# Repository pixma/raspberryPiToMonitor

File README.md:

raspberryPiToMonitor
====================

An Energy monitoring System based on RaspberryPi B Model.

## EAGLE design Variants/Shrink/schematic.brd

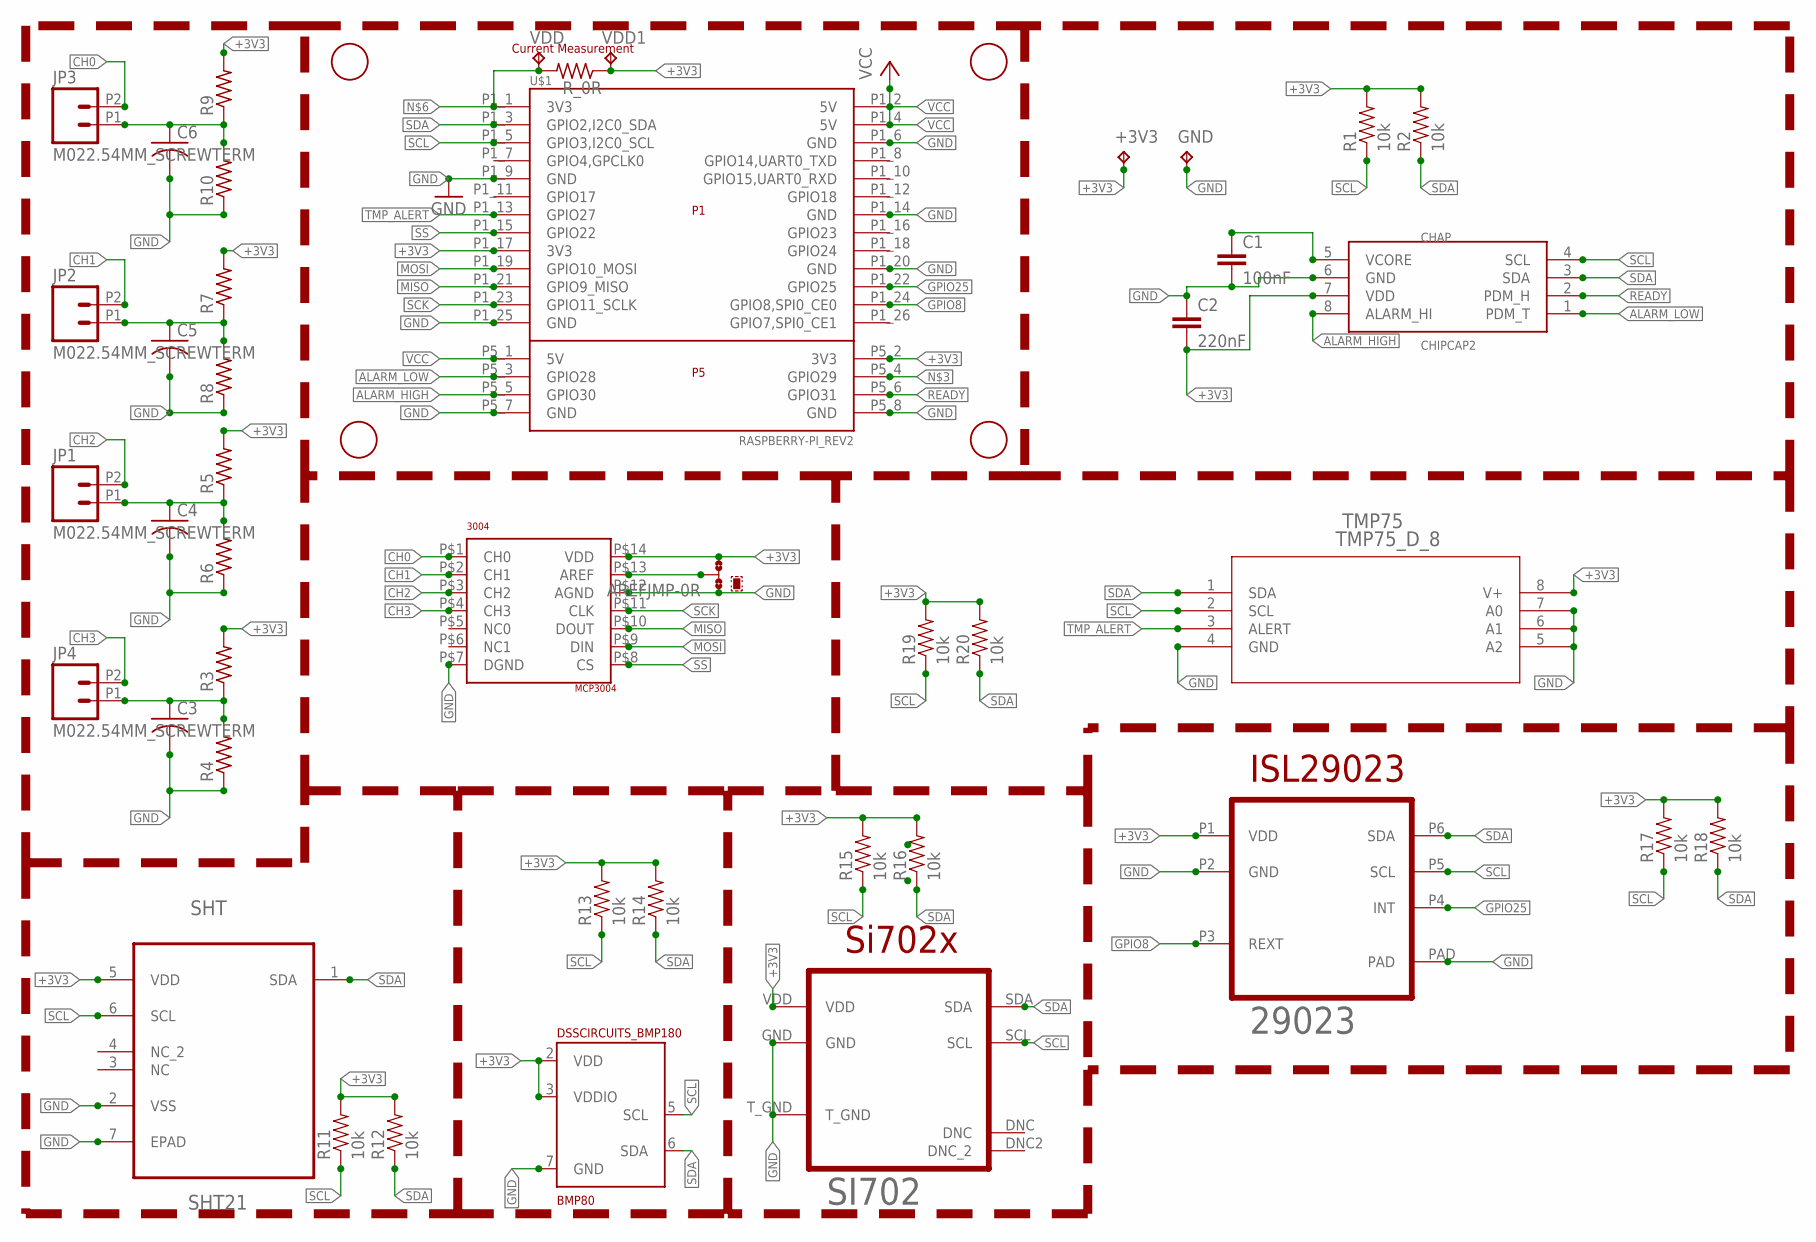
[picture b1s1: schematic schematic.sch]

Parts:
3004: MCP3004; TSSOP14_4MM4
29023: ISL29023; ODFN6
+3V3: TPTP20R; TP20R
AREFJMP: 0R-JUMPA; A0R-JMP
BMP80: DSSCIRCUITS_BMP180; DSSCIRCUITS_LGA7
C1: 100nF; 0402-CAP
C2: 220nF; 0402-CAP
C3, C4, C5, C6: C-USC0402; C0402
CHAP: CHIPCAP2
GND: TPTP20R; TP20R
JP1, JP2, JP3, JP4: M022.54MM_SCREWTERM; 1X02_2.54_SCREWTERM
R1, R2, R11, R12, R13, R14, R15, R16, R17, R18, R19, R20: 10k; 0603-RES
R3, R4, R5, R6, R7, R8, R9, R10: R-US_R0402; R0402
R_0R: R-US_R0402; R0402
SHT: SHT21; DFN300X300X110-7N
SI702: SI702X; DFN6
TMP75: TMP75_D_8; D8
U$1: RASPBERRY-PI_REV2
U$2, U$3, U$4, U$5: FIDUCIAL; FIDUCIAL_1MM
VDD, VDD1: TPTP20R; TP20R

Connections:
+3V3: 3004.P$14 (VDD), 29023.P1 (VDD), +3V3.TP, AREFJMP.3, BMP80.2 (VDD), BMP80.3 (VDDIO), C2.2, CHAP.7 (VDD), R1.2, R2.2, R3.2, R5.2, R7.2, R9.2, R11.2, R12.2, R13.2, R14.2, R15.2, R16.2, R17.2, R18.2, R19.2, R20.2, R_0R.1, SHT.5 (VDD), SI702.VDD, TMP75.8 (V+), U$1.P1_17 (3V3), U$1.P5_2 (3V3), VDD1.TP
ALARM_HIGH: CHAP.8 (ALARM_HI), U$1.P5_5 (GPIO30)
ALARM_LOW: CHAP.1 (PDM_T), U$1.P5_3 (GPIO28)
CH0: 3004.P$1 (CH0), JP3.P2 (2)
CH1: 3004.P$2 (CH1), JP2.P2 (2)
CH2: 3004.P$3 (CH2), JP1.P2 (2)
CH3: 3004.P$4 (CH3), JP4.P2 (2)
GND: 3004.P$7 (DGND), 3004.P$12 (AGND), 29023.P2 (GND), 29023.PAD, AREFJMP.1, BMP80.7 (GND), C1.2, C2.1, C3.2, C4.2, C5.2, C6.2, CHAP.6 (GND), GND.TP, R4.1, R6.1, R8.1, R10.1, SHT.2 (VSS), SHT.7 (EPAD), SI702.GND, SI702.T_GND, TMP75.4 (GND), TMP75.5 (A2), TMP75.6 (A1), TMP75.7 (A0), U$1.P1_6 (GND), U$1.P1_9 (GND), U$1.P1_14 (GND), U$1.P1_20 (GND), U$1.P1_25 (GND), U$1.P5_7 (GND), U$1.P5_8 (GND)
GPIO8: 29023.P3 (REXT), U$1.P1_24 (GPIO8,SPI0_CE0)
GPIO25: 29023.P4 (INT), U$1.P1_22 (GPIO25)
MISO: 3004.P$10 (DOUT), U$1.P1_21 (GPIO9_MISO)
MOSI: 3004.P$9 (DIN), U$1.P1_19 (GPIO10_MOSI)
unnamed: C4.1, JP1.P1 (1), R5.1, R6.2
unnamed: C5.1, JP2.P1 (1), R7.1, R8.2
unnamed: C6.1, JP3.P1 (1), R9.1, R10.2
unnamed: C1.1, CHAP.5 (VCORE)
unnamed: R_0R.2, U$1.P1_1 (3V3), VDD.TP
unnamed: C3.1, JP4.P1 (1), R3.1, R4.2
unnamed: 3004.P$13 (AREF), AREFJMP.2
READY: CHAP.2 (PDM_H), U$1.P5_6 (GPIO31)
SCK: 3004.P$11 (CLK), U$1.P1_23 (GPIO11_SCLK)
SCL: 29023.P5 (SCL), BMP80.5 (SCL), CHAP.4 (SCL), R1.1, R11.1, R13.1, R15.1, R17.1, R19.1, SHT.6 (SCL), SI702.SCL, TMP75.2 (SCL), U$1.P1_5 (GPIO3,I2C0_SCL)
SDA: 29023.P6 (SDA), BMP80.6 (SDA), CHAP.3 (SDA), R2.1, R12.1, R14.1, R16.1, R18.1, R20.1, SHT.1 (SDA), SI702.SDA, TMP75.1 (SDA), U$1.P1_3 (GPIO2,I2C0_SDA)
SS: 3004.P$8 (CS), U$1.P1_15 (GPIO22)
TMP_ALERT: TMP75.3 (ALERT), U$1.P1_13 (GPIO27)
VCC: U$1.P1_2 (5V), U$1.P1_4 (5V), U$1.P5_1 (5V)

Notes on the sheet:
Current Measurement

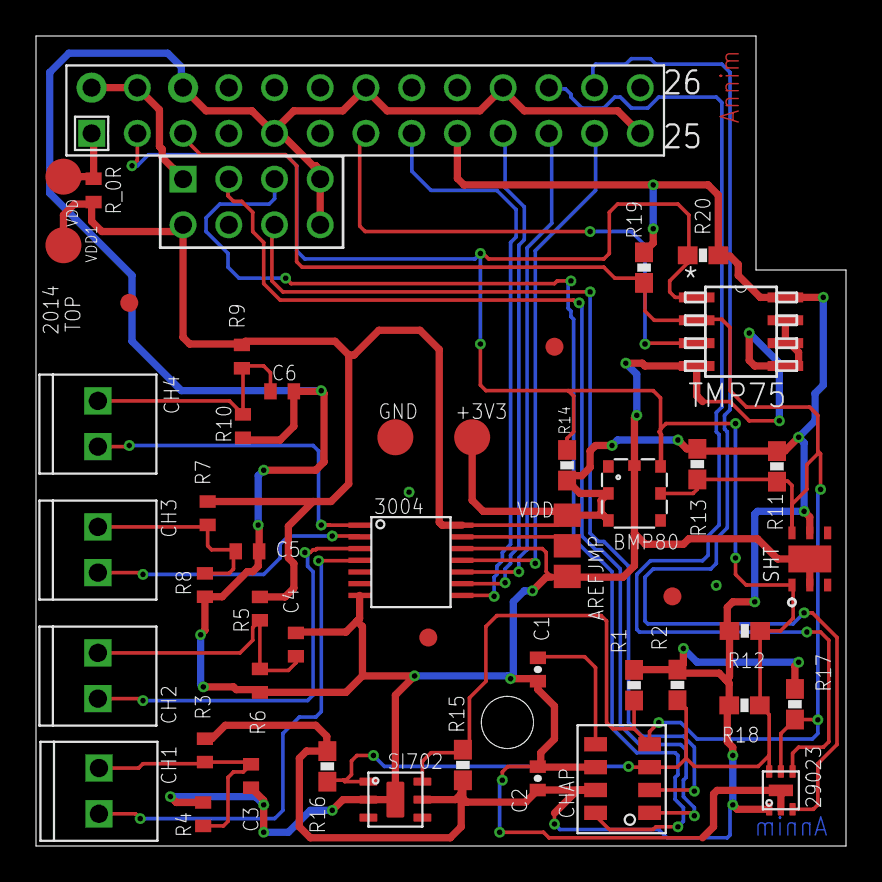
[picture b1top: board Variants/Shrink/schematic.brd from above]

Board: 2 copper layers, 45.0 x 45.0 mm, 48 parts (0 on the bottom side), 26 nets.

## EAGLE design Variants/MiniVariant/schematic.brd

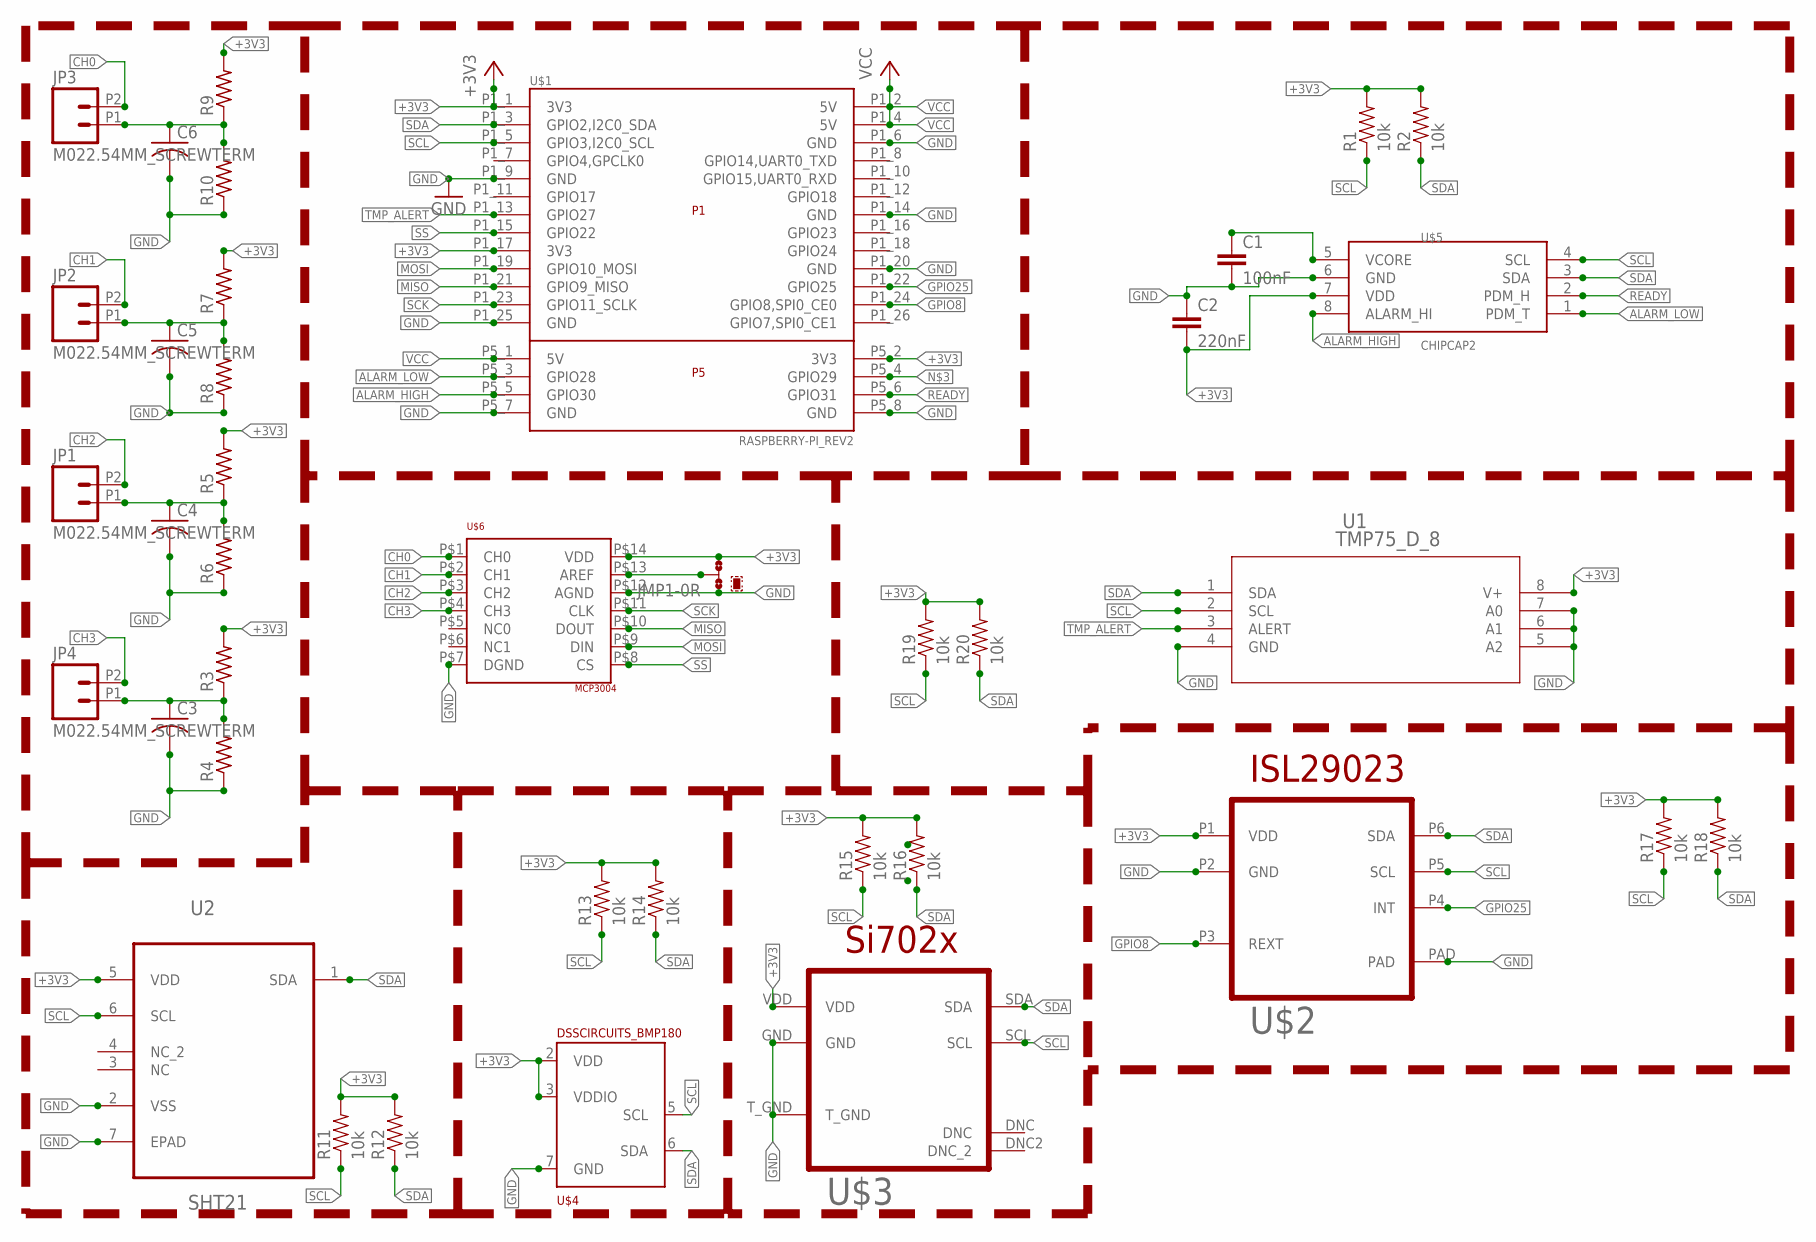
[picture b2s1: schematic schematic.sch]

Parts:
C1: 100nF; 0402-CAP
C2: 220nF; 0402-CAP
C3, C4, C5, C6: C-USC0402; C0402
JMP1: 0R-JUMPA; A0R-JMP
JP1, JP2, JP3, JP4: M022.54MM_SCREWTERM; 1X02_2.54_SCREWTERM
R1, R2, R11, R12, R13, R14, R15, R16, R17, R18, R19, R20: 10k; 0603-RES
R3, R4, R5, R6, R7, R8, R9, R10: R-US_R0402; R0402
U1: TMP75_D_8; D8
U2: SHT21; DFN300X300X110-7N
U$1: RASPBERRY-PI_REV2
U$2: ISL29023; ODFN6
U$3: SI702X; DFN6
U$4: DSSCIRCUITS_BMP180; DSSCIRCUITS_LGA7
U$5: CHIPCAP2
U$6: MCP3004; TSSOP14_4MM4

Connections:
+3V3: C2.2, JMP1.3, R1.2, R2.2, R3.2, R5.2, R7.2, R9.2, R11.2, R12.2, R13.2, R14.2, R15.2, R16.2, R17.2, R18.2, R19.2, R20.2, U1.8 (V+), U2.5 (VDD), U$1.P1_1 (3V3), U$1.P1_17 (3V3), U$1.P5_2 (3V3), U$2.P1 (VDD), U$3.VDD, U$4.2 (VDD), U$4.3 (VDDIO), U$5.7 (VDD), U$6.P$14 (VDD)
ALARM_HIGH: U$1.P5_5 (GPIO30), U$5.8 (ALARM_HI)
ALARM_LOW: U$1.P5_3 (GPIO28), U$5.1 (PDM_T)
CH0: JP3.P2 (2), U$6.P$1 (CH0)
CH1: JP2.P2 (2), U$6.P$2 (CH1)
CH2: JP1.P2 (2), U$6.P$3 (CH2)
CH3: JP4.P2 (2), U$6.P$4 (CH3)
GND: C1.2, C2.1, C3.2, C4.2, C5.2, C6.2, JMP1.1, R4.1, R6.1, R8.1, R10.1, U1.4 (GND), U1.5 (A2), U1.6 (A1), U1.7 (A0), U2.2 (VSS), U2.7 (EPAD), U$1.P1_6 (GND), U$1.P1_9 (GND), U$1.P1_14 (GND), U$1.P1_20 (GND), U$1.P1_25 (GND), U$1.P5_7 (GND), U$1.P5_8 (GND), U$2.P2 (GND), U$2.PAD, U$3.GND, U$3.T_GND, U$4.7 (GND), U$5.6 (GND), U$6.P$7 (DGND), U$6.P$12 (AGND)
GPIO8: U$1.P1_24 (GPIO8,SPI0_CE0), U$2.P3 (REXT)
GPIO25: U$1.P1_22 (GPIO25), U$2.P4 (INT)
MISO: U$1.P1_21 (GPIO9_MISO), U$6.P$10 (DOUT)
MOSI: U$1.P1_19 (GPIO10_MOSI), U$6.P$9 (DIN)
unnamed: C4.1, JP1.P1 (1), R5.1, R6.2
unnamed: C5.1, JP2.P1 (1), R7.1, R8.2
unnamed: C6.1, JP3.P1 (1), R9.1, R10.2
unnamed: C1.1, U$5.5 (VCORE)
unnamed: C3.1, JP4.P1 (1), R3.1, R4.2
unnamed: JMP1.2, U$6.P$13 (AREF)
READY: U$1.P5_6 (GPIO31), U$5.2 (PDM_H)
SCK: U$1.P1_23 (GPIO11_SCLK), U$6.P$11 (CLK)
SCL: R1.1, R11.1, R13.1, R15.1, R17.1, R19.1, U1.2 (SCL), U2.6 (SCL), U$1.P1_5 (GPIO3,I2C0_SCL), U$2.P5 (SCL), U$3.SCL, U$4.5 (SCL), U$5.4 (SCL)
SDA: R2.1, R12.1, R14.1, R16.1, R18.1, R20.1, U1.1 (SDA), U2.1 (SDA), U$1.P1_3 (GPIO2,I2C0_SDA), U$2.P6 (SDA), U$3.SDA, U$4.6 (SDA), U$5.3 (SDA)
SS: U$1.P1_15 (GPIO22), U$6.P$8 (CS)
TMP_ALERT: U1.3 (ALERT), U$1.P1_13 (GPIO27)
VCC: U$1.P1_2 (5V), U$1.P1_4 (5V), U$1.P5_1 (5V)

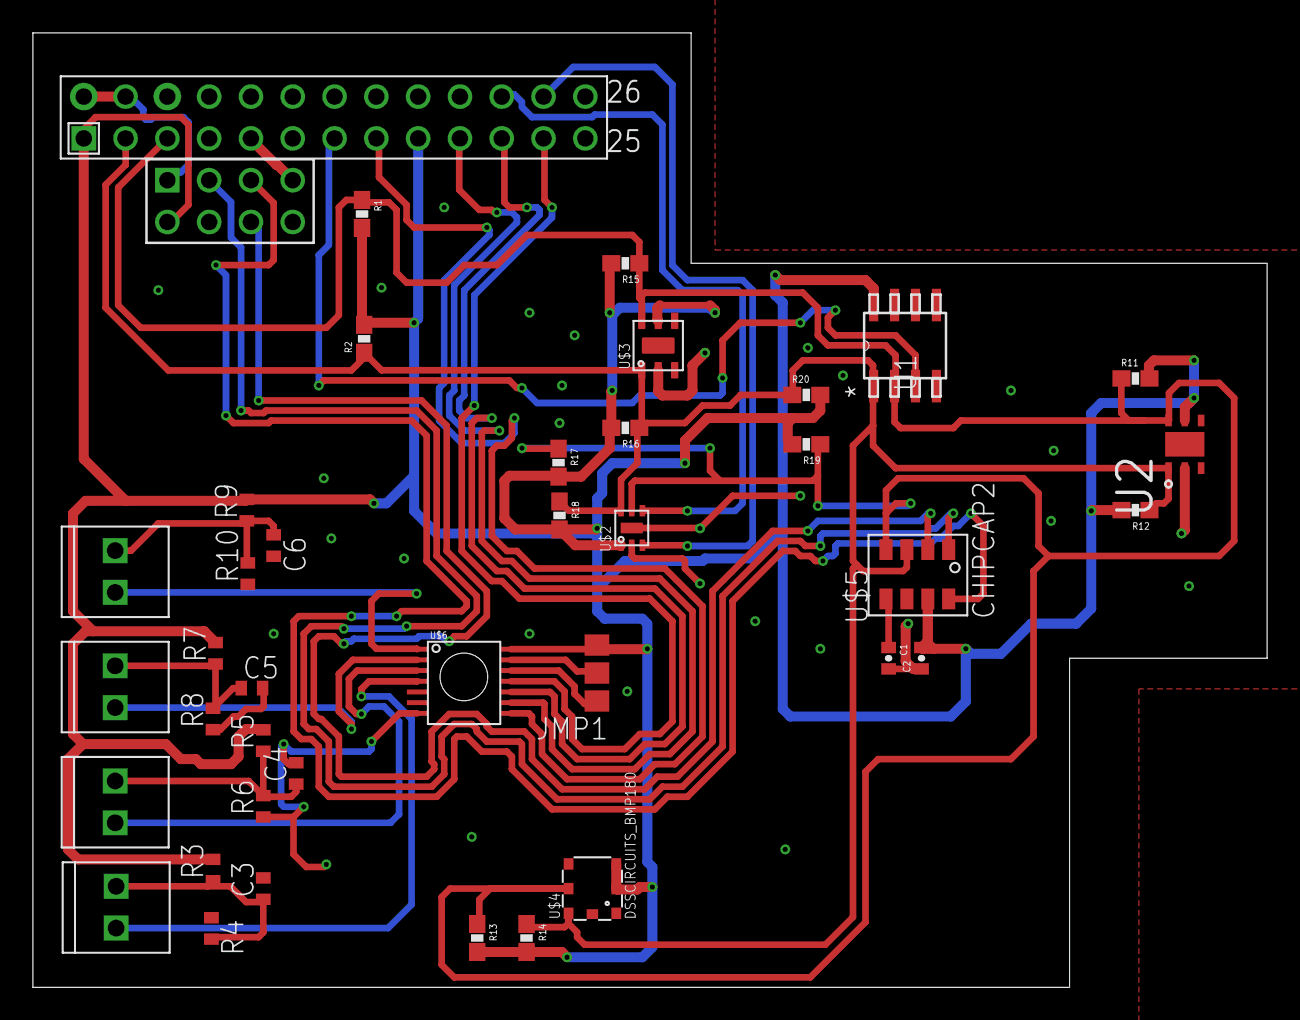
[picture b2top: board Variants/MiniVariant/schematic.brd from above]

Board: 2 copper layers, 75.0 x 58.0 mm, 39 parts (0 on the bottom side), 25 nets.

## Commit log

2014-08-11 Initial Commit.
2014-08-30 Normal Push
2014-10-27 normal Push.

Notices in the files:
parts and their libraries:
SparkFun-Connectors: Licensing: Creative Commons ShareAlike 4.0 International - https://creativecommons.org/licenses/by-sa/4.0
